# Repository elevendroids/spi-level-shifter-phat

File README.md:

# SPI Level Shifter pHAT

An expansion board for Raspberry Pi Zero / 2 / 3 / 4 and other pin-compatible SBCs.

Provides a configurable SPI interface with a level shifter to communicate with 3.3V and 1.8V logic level devices.

In addition, this board can also be used as a SPI NOR Flash in-system programmer - target power supply and interface can be controlled in software to avoid interference with a running system.

# Features

- independent 3.3V and 1.8V power supplies, target voltage selectable by a jumper
- high speed logic level translator - rated up to 380Mbit/s (Note that the actual max. speed is limited by the SBC's capabilities, length and quality of the connection cable to the target and the target itself)
- support for powered-off operation - the interface stays isolated while either the SBC is powered off or the interface is disabled by software
- configurable interface control: the translator and target power supply may be disabled by either one of two different GPIO pins or may be enabled permanently
- selectable /CS pin source: SPI0 /CE0, SPI0 /CE1 or GPIO6 (on RPi)
- 6-pin IDC target connector, pin-compatible with the standard 8-pin ISP connector for SPI NOR Flash memories

Designed in KiCad 5.1.7

PCB render:

Prototype PCB:

Schematic: [PDF](docs/spi-level-shifter-phat.pdf)

License: [CC BY-SA 4.0](https://creativecommons.org/licenses/by-sa/4.0/)

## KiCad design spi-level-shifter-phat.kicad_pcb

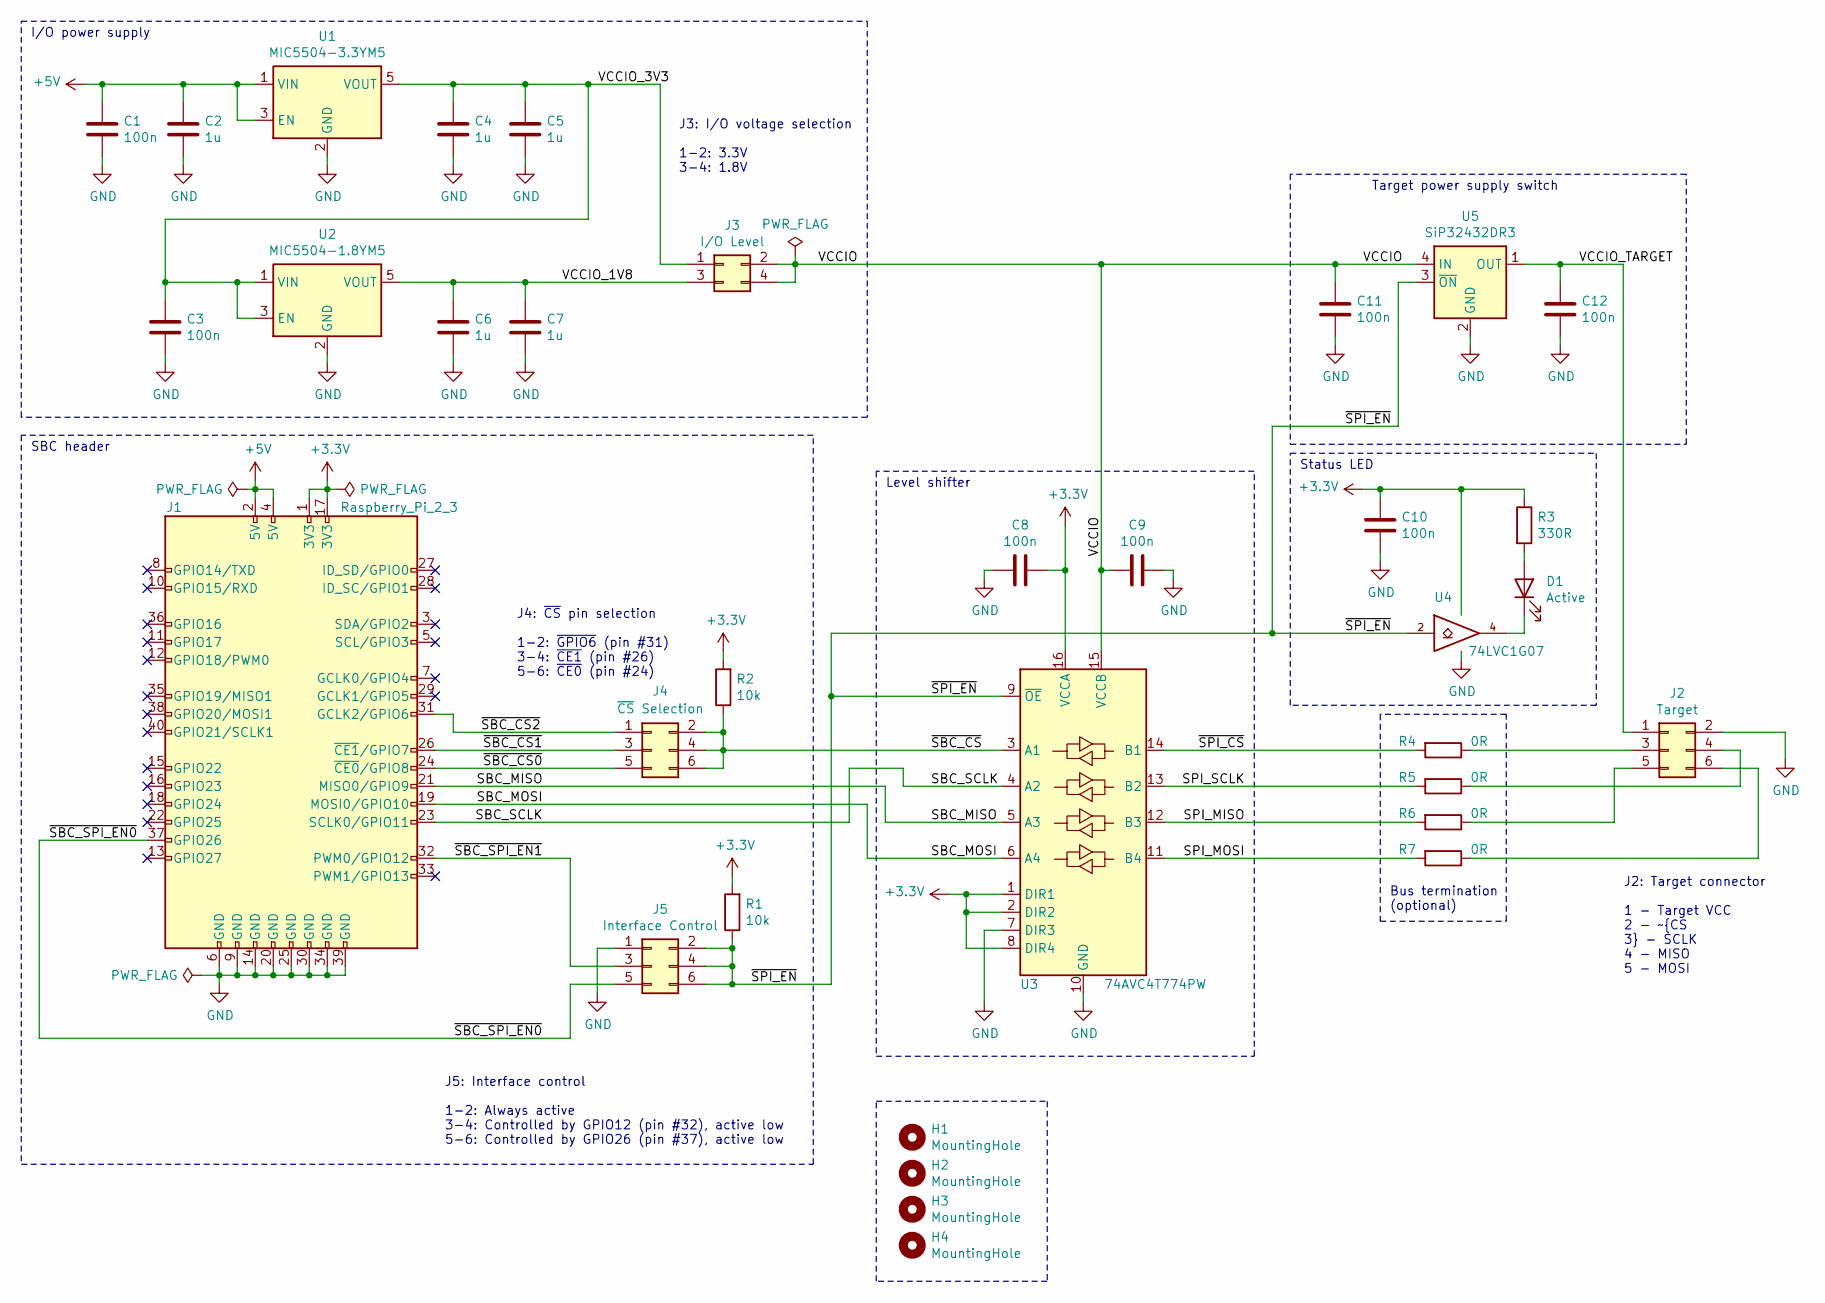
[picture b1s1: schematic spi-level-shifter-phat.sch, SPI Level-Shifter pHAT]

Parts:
C1, C3, C8, C9, C10, C11, C12: 100n; C_0603_1608Metric
C2, C4, C5, C6, C7: 1u; C_0603_1608Metric
D1: Active; LED_0805_2012Metric
H1, H2, H3, H4: MountingHole; MountingHole_2.7mm_M2.5
J1: Raspberry_Pi_2_3; PinSocket_2x20_P2.54mm_Vertical
J2: Target; IDC-Header_2x03_P2.54mm_Vertical
J3: I/O Level; PinHeader_2x02_P2.00mm_Vertical
J4: ~CS~ Selection; PinHeader_2x03_P2.00mm_Vertical
J5: Interface Control; PinHeader_2x03_P2.00mm_Vertical
R1, R2: 10k; R_0603_1608Metric
R3: 330R; R_0603_1608Metric
R4, R5, R6, R7: 0R; R_0402_1005Metric
U1: MIC5504-3.3YM5; SOT-23-5
U2: MIC5504-1.8YM5; SOT-23-5
U3: 74AVC4T774PW; TSSOP-16_4.4x5mm_P0.65mm
U4: 74LVC1G07; SOT-353_SC-70-5
U5: SiP32432DR3; SOT-363_SC-70-6

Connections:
+3V3: C8.1, C10.1, J1.1 (3V3), J1.17 (3V3), R1.2, R2.2, R3.1, U3.1 (DIR1), U3.2 (DIR2), U3.8 (DIR4), U3.16 (VCCA), U4.5 (VCC)
+5V: C1.1, C2.1, J1.2 (5V), J1.4 (5V), U1.1 (VIN), U1.3 (EN)
/SBC_MISO: J1.21 (MISO0/GPIO9), U3.5 (A3)
/SBC_MOSI: J1.19 (MOSI0/GPIO10), U3.6 (A4)
/SBC_SCLK: J1.23 (SCLK0/GPIO11), U3.4 (A2)
/SPI_MISO: R6.2, U3.12 (B3)
/SPI_MOSI: R7.2, U3.11 (B4)
/SPI_SCLK: R5.2, U3.13 (B2)
/VCCIO: C9.1, C11.1, J3.2, J3.4, U3.15 (VCCB), U5.4 (IN)
/VCCIO_1V8: C6.1, C7.1, J3.3, U2.5 (VOUT)
/VCCIO_3V3: C3.1, C4.1, C5.1, J3.1, U1.5 (VOUT), U2.1 (VIN), U2.3 (EN)
/VCCIO_TARGET: C12.1, J2.1, U5.1 (OUT)
/~SBC_CS: J4.2, J4.4, J4.6, R2.1, U3.3 (A1)
/~SBC_CS0: J1.24 (~CE0~/GPIO8), J4.5
/~SBC_CS1: J1.26 (~CE1~/GPIO7), J4.3
/~SBC_CS2: J1.31 (GCLK2/GPIO6), J4.1
/~SBC_SPI_EN0: J1.37 (GPIO26), J5.5
/~SBC_SPI_EN1: J1.32 (PWM0/GPIO12), J5.3
/~SPI_CS: R4.2, U3.14 (B1)
/~SPI_EN: J5.2, J5.4, J5.6, R1.1, U3.9 (~OE), U4.2, U5.3 (~ON)
GND: C1.2, C2.2, C3.2, C4.2, C5.2, C6.2, C7.2, C8.2, C9.2, C10.2, C11.2, C12.2, J1.6 (GND), J1.9 (GND), J1.14 (GND), J1.20 (GND), J1.25 (GND), J1.30 (GND), J1.34 (GND), J1.39 (GND), J2.2, J5.1, U1.2 (GND), U2.2 (GND), U3.7 (DIR3), U3.10 (GND), U4.3 (GND), U5.2 (GND), U5.5 (GND)
unnamed: D1.1 (K), U4.4
unnamed: D1.2 (A), R3.2
unnamed: J2.3, R4.1
unnamed: J2.4, R5.1
unnamed: J2.5, R6.1
unnamed: J2.6, R7.1

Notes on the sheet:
Target power supply switch
J2: Target connector 1 - Target VCC 2 - ~CS 3 - SCLK 4 - MISO 5 - MOSI
Bus termination (optional)
Status LED
I/O power supply
Level shifter
SBC header
J5: Interface control 1-2: Always active 3-4: Controlled by GPIO12 (pin #32), active low 5-6: Controlled by GPIO26 (pin #37), active low
J4: ~CS~ pin selection 1-2: ~GPIO6~ (pin #31) 3-4: ~CE1~ (pin #26) 5-6: ~CE0~ (pin #24)
J3: I/O voltage selection 1-2: 3.3V 3-4: 1.8V

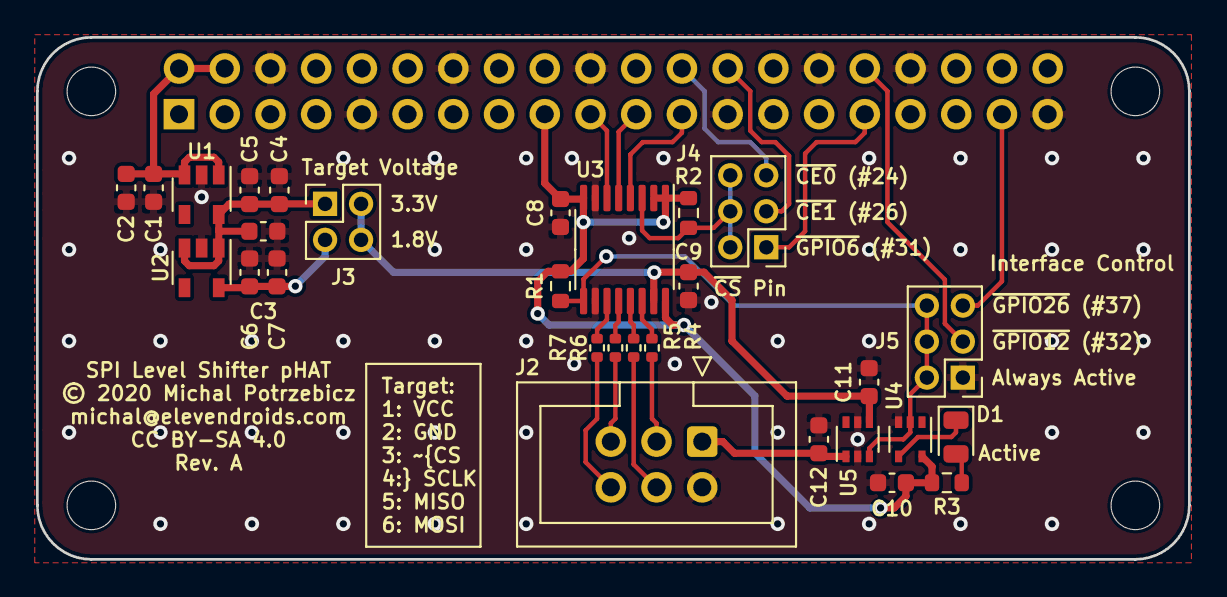
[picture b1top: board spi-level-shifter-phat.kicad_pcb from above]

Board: 2 copper layers, 64.0 x 29.0 mm, 34 parts (1 on the bottom side), 27 nets.

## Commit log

2020-10-27 Added README
2021-03-22 Updated README, added photo of a prototype
2021-04-07 Updated schematic due to library changes to 74AVC4T774PW

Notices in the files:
spi-level-shifter-phat.kicad_pcb:
© 2020 Michal Potrzebicz
CC BY-SA 4.0
